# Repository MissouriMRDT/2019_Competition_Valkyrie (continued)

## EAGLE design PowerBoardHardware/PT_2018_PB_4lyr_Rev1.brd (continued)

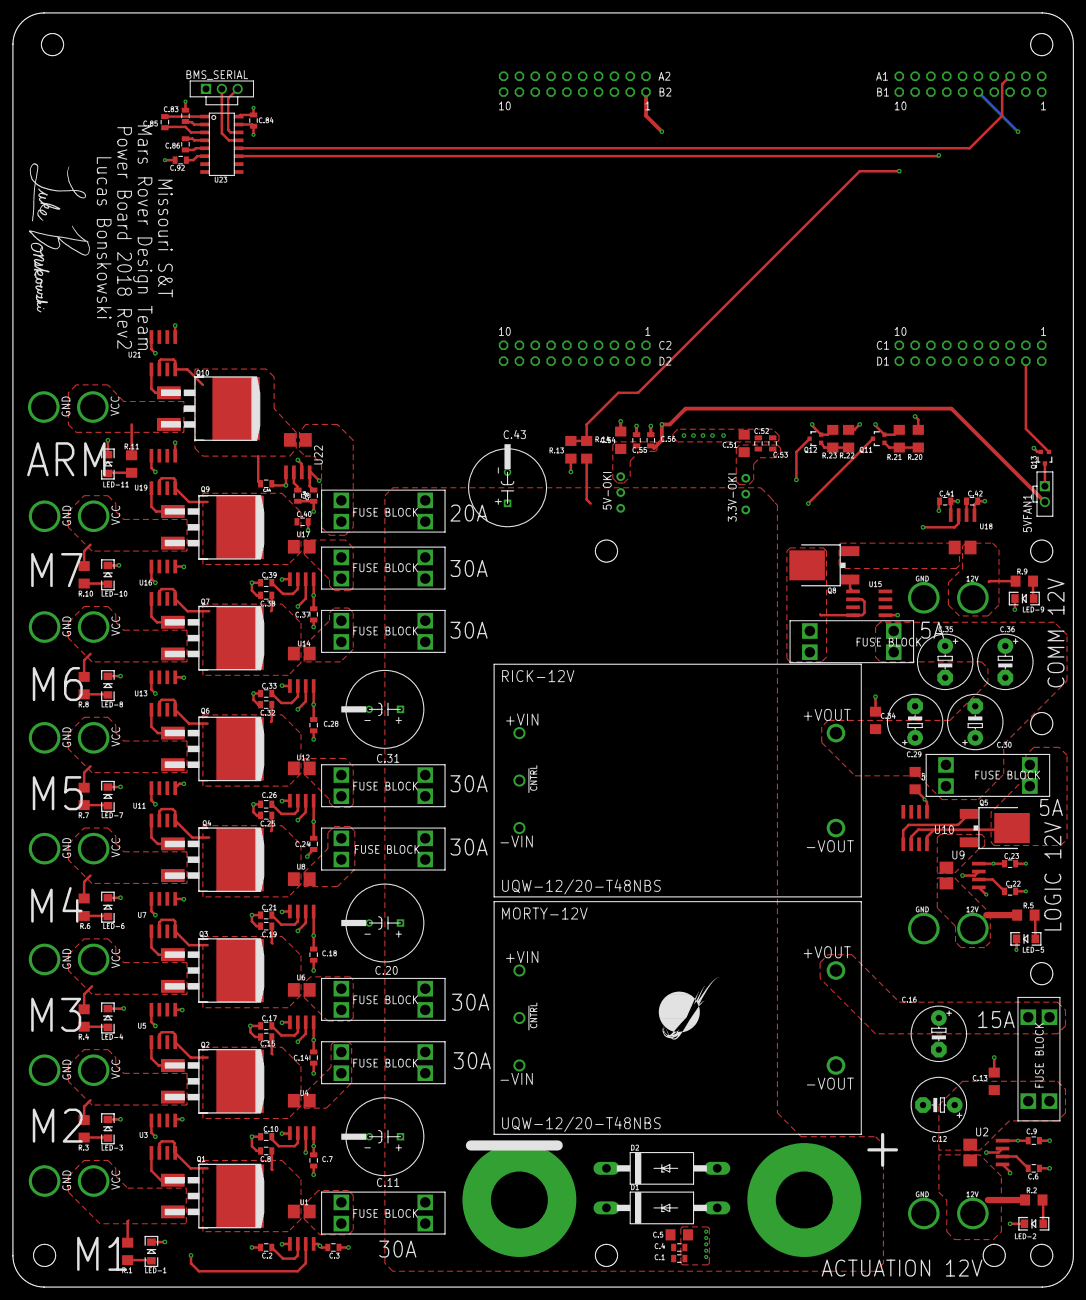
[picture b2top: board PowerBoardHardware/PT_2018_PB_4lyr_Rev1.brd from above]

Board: 4 copper layers, 170.2 x 204.5 mm, 165 parts (0 on the bottom side), 108 nets.

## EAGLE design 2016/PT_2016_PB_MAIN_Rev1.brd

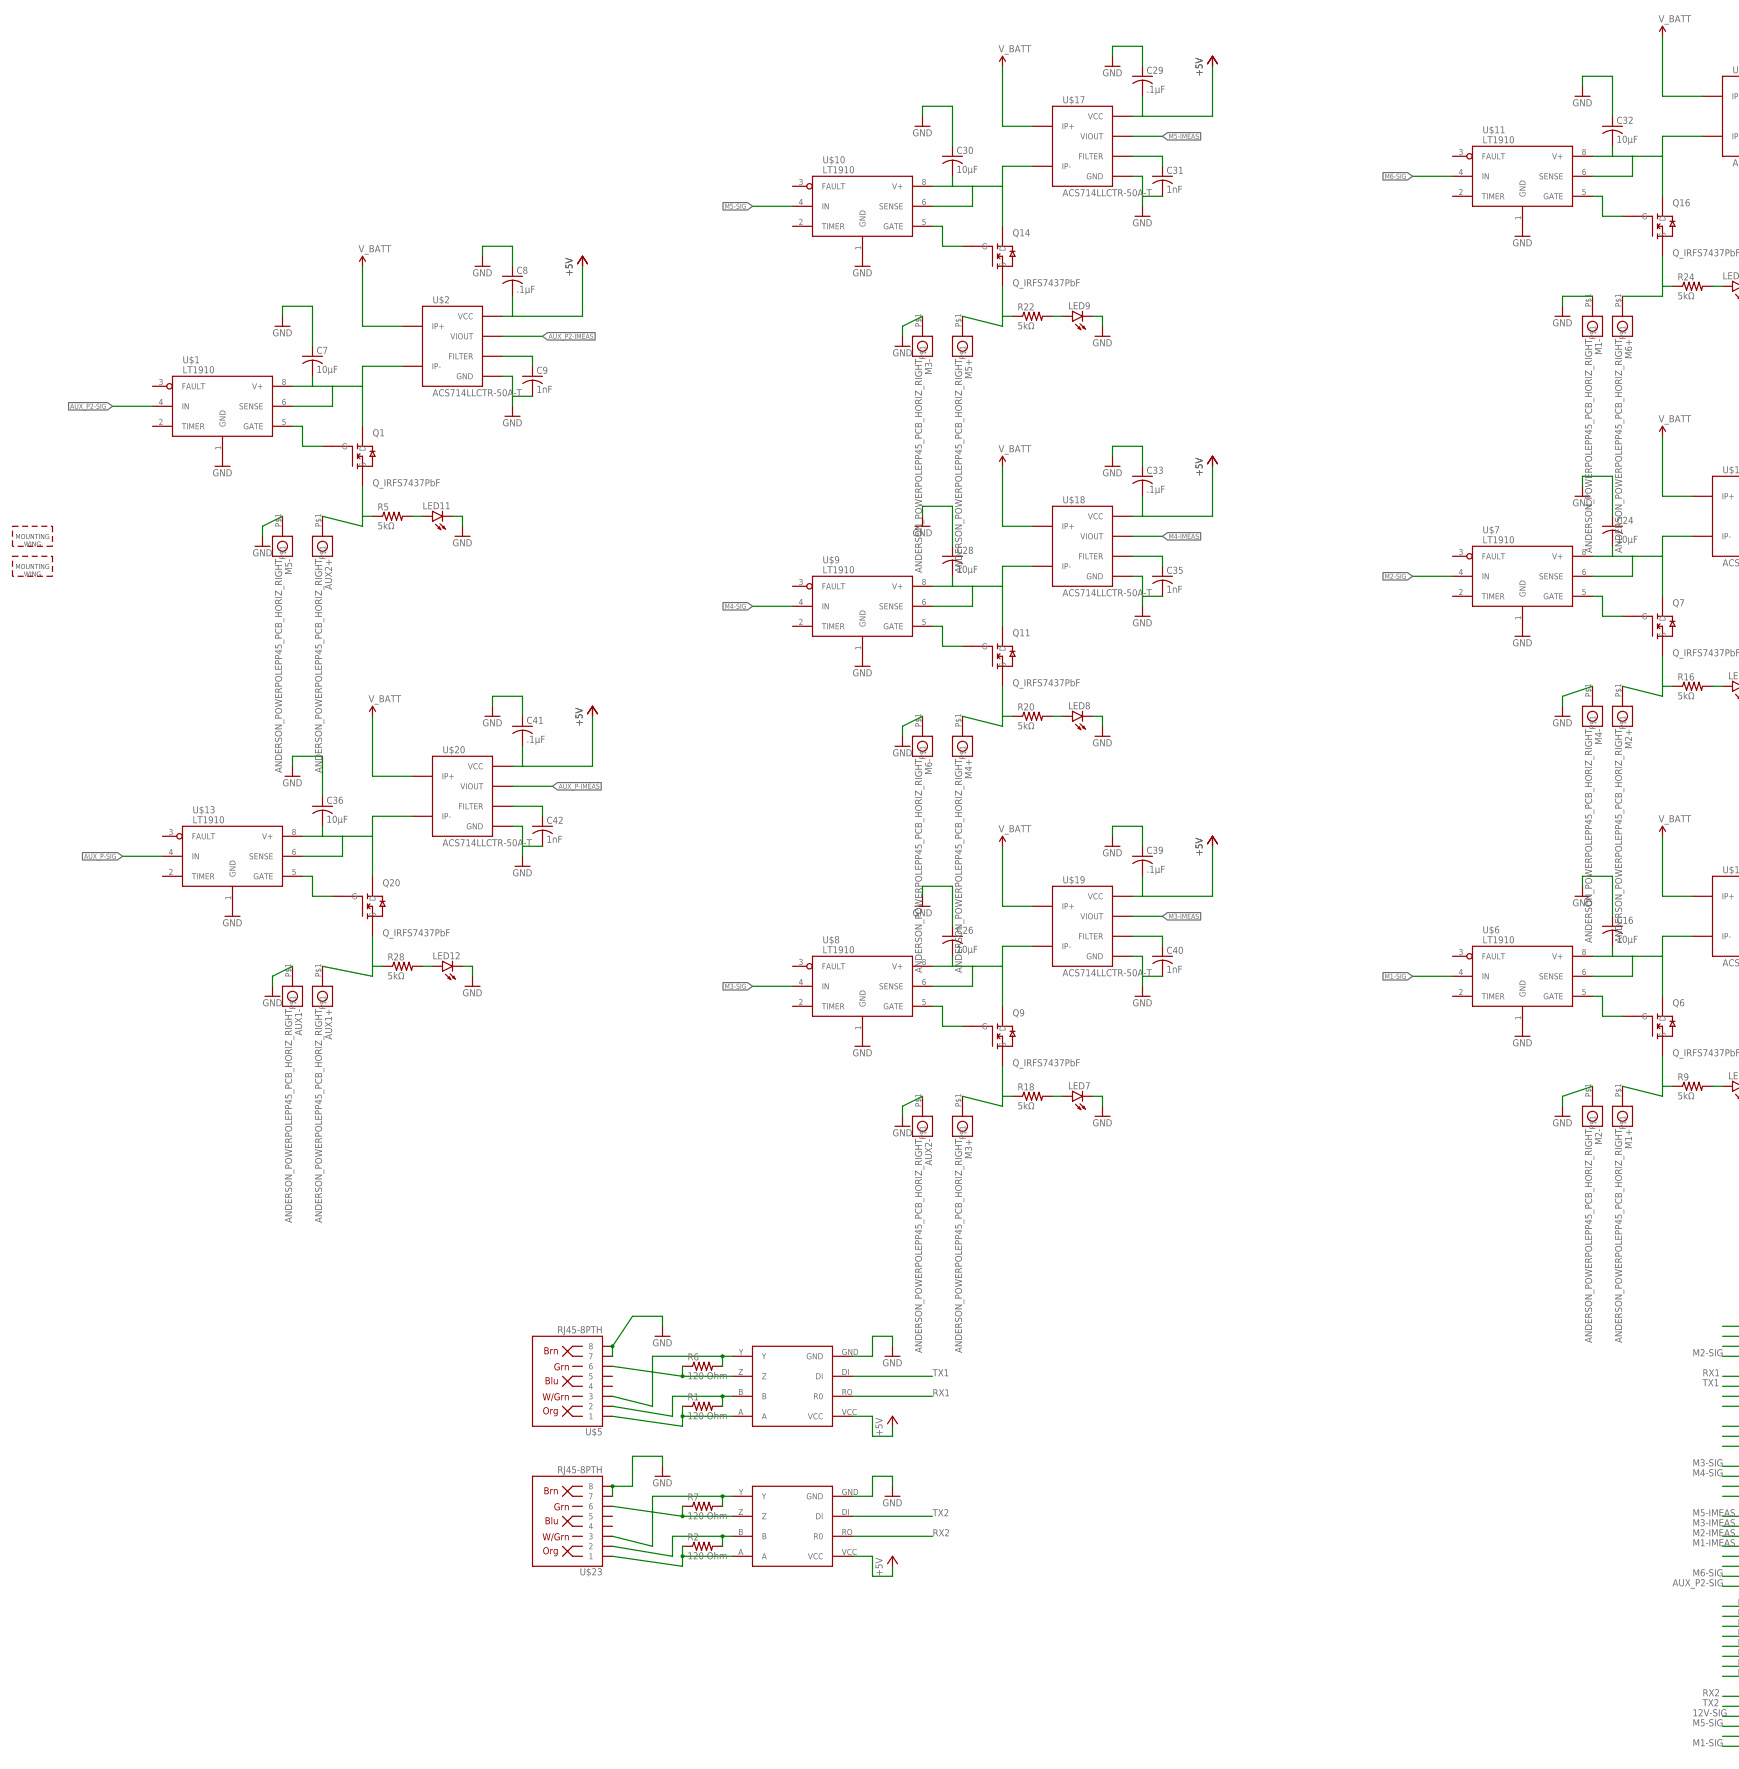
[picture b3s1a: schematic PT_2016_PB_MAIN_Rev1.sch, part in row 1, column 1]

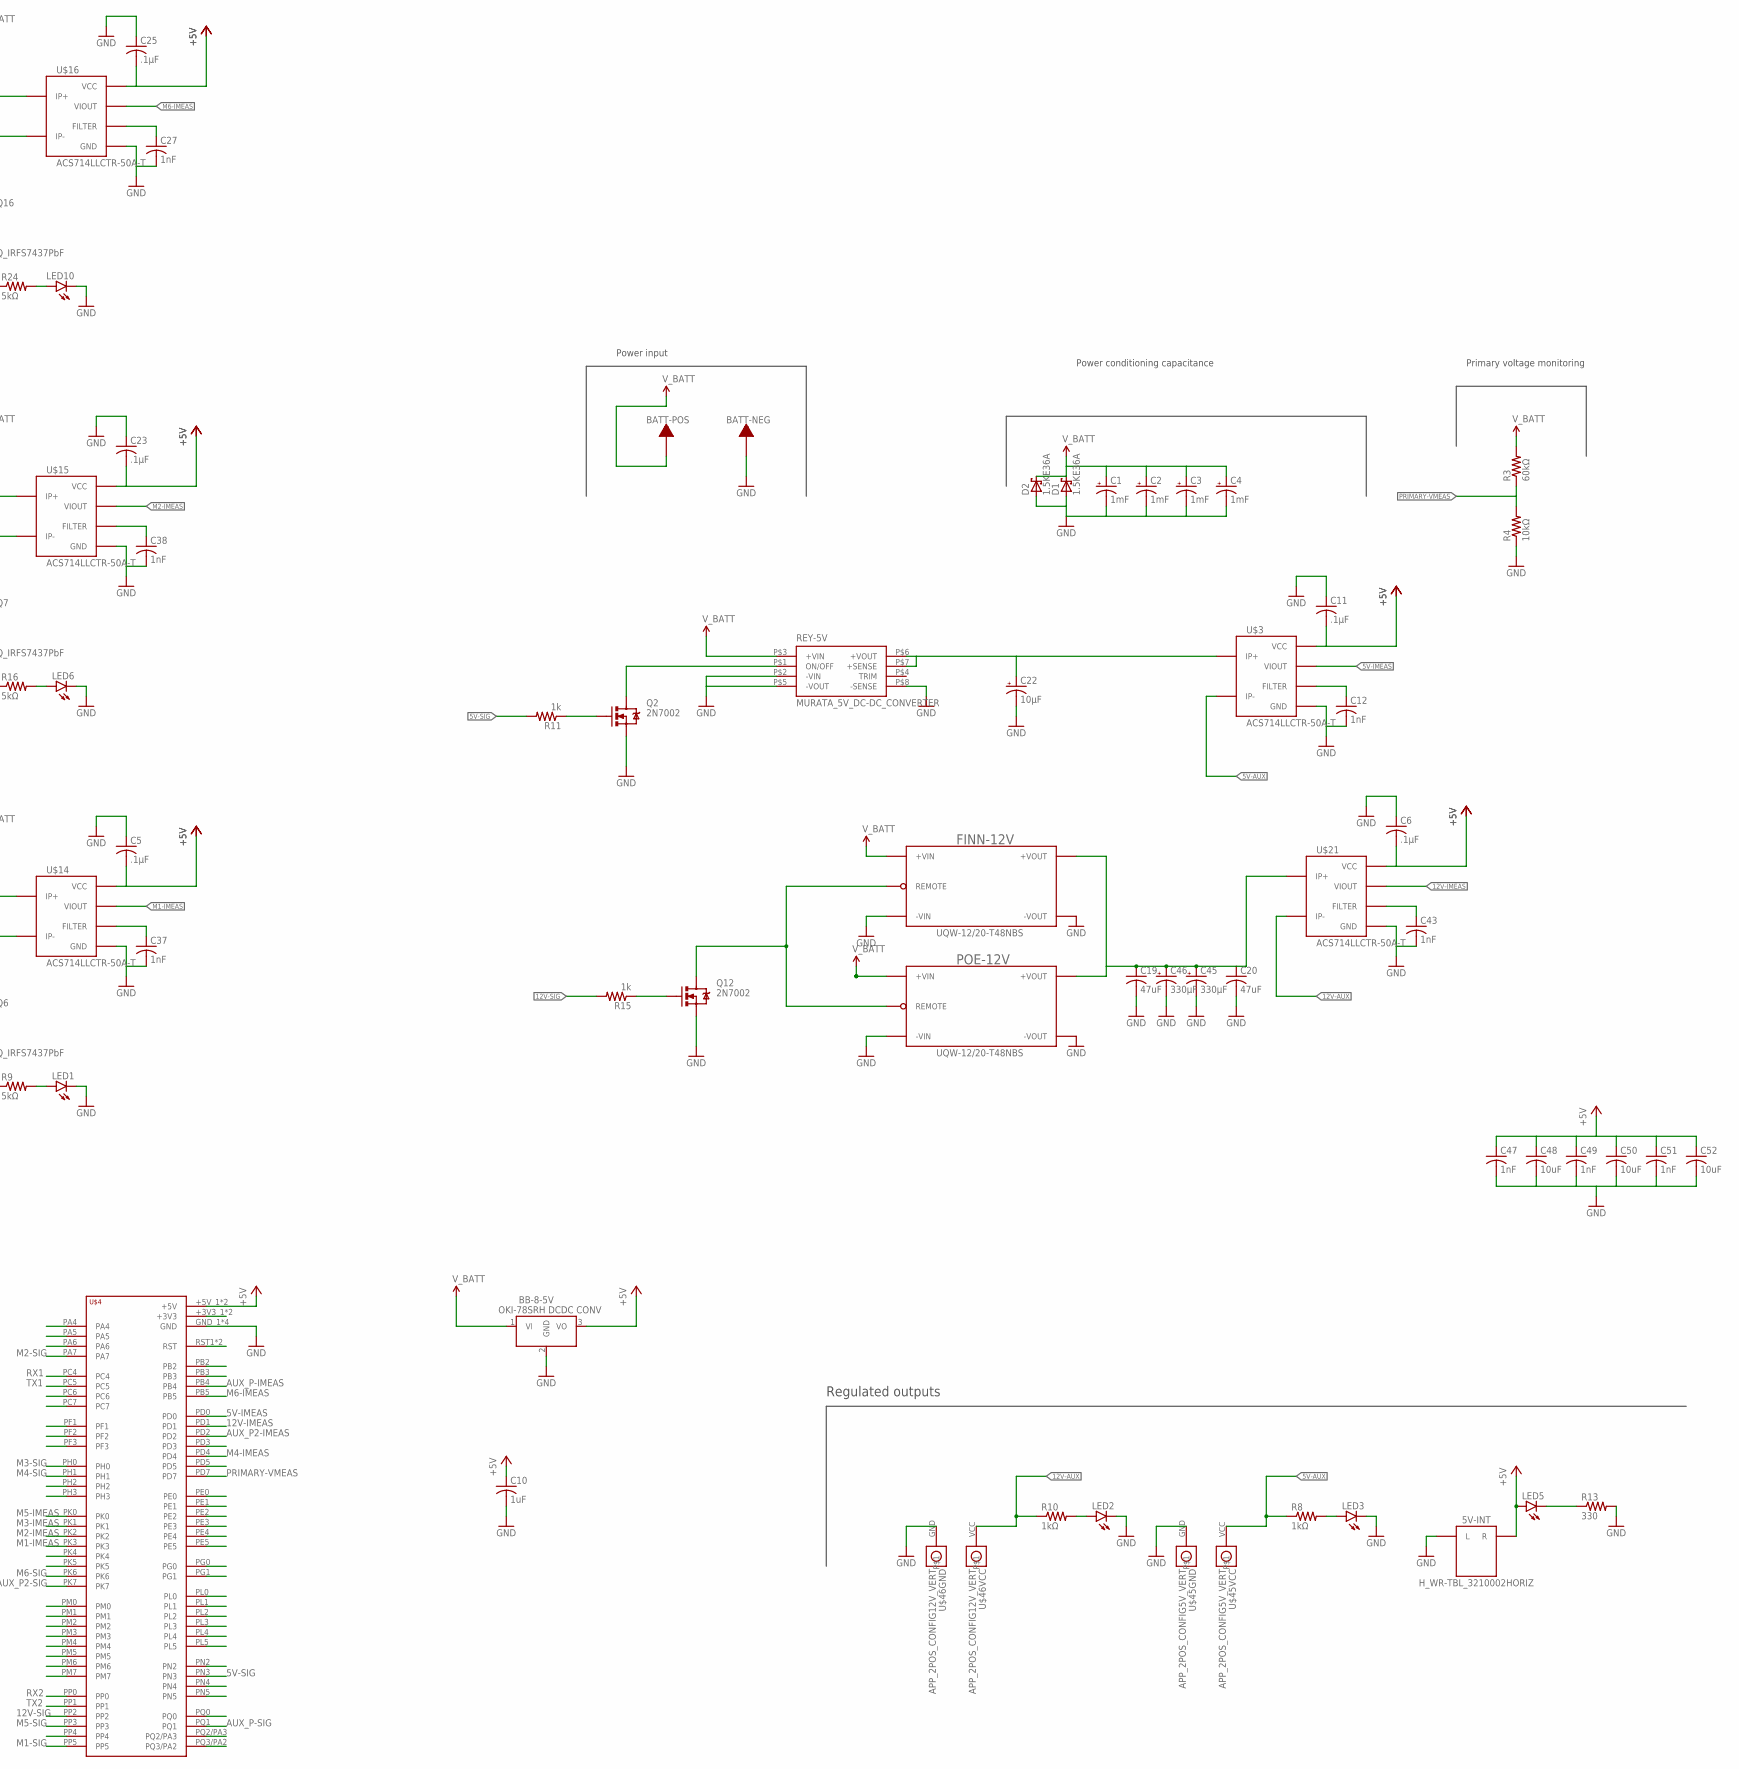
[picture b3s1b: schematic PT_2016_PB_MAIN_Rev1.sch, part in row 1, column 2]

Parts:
5V-INT: H_WR-TBL_3210002HORIZ; 691322110002
AUX1+, AUX1-, AUX2+, AUX2-: ANDERSON_POWERPOLEPP45_PCB_HORIZ_RIGHT; APP45_PCB_HORIZ_RIGHT
BATT-NEG: TERMINAL_HOLE; LARGE_TERMINAL_HOLE
BATT-POS: TERMINAL_HOLE; LARGE_TERMINAL_HOLE
BB-8-5V: Q_OKI-78SR; OKI-78SRH
C1, C2, C3, C4: 1mF; C_12.5MM
C5, C6, C8, C11, C23, C25, C29, C33, C39, C41: .1µF; C1206
C7, C16, C24, C26, C28, C30, C32, C36: 10µF; C1206
C9, C12, C27, C31, C35, C37, C38, C40, C42, C43, C47, C49, C51: 1nF; C1206
C10: 1uF; C1206
C19, C20: 47uF; C1206
C22: 10µF; E5-8,5
C45, C46: 330µF; E5-8,5
C48, C50, C52: 10uF; C1206
D1, D2: 1.5KE36A; CB429-17
FINN-12V: UQW-12/20-T48NBS; U-T48-QB-NO_TRIM
LED1, LED2, LED3, LED5, LED6, LED7, LED8, LED9, LED10, LED11, LED12: LED1206; LED-1206
M1+, M1-, M2+, M2-, M3+, M3-, M4+, M4-, M5+, M5-, M6+, M6-: ANDERSON_POWERPOLEPP45_PCB_HORIZ_RIGHT; APP45_PCB_HORIZ_RIGHT
POE-12V: UQW-12/20-T48NBS; U-T48-QB-NO_TRIM
Q1, Q6, Q7, Q9, Q11, Q14, Q16, Q20: Q_IRFS7437PbF; D2PACK
Q2, Q12: 2N7002; SOT323
R1, R2, R6, R7: 120 Ohm; 1206
R3: 60kΩ; R1206
R4: 10kΩ; R1206
R5, R9, R16, R18, R20, R22, R24, R28: 5kΩ; 1206
R8, R10: 1kΩ; 1206
R11, R15: 1k; R1206
R13: 330; 1206
REY-5V: MURATA_5V_DC-DC_CONVERTER
U$1, U$6, U$7, U$8, U$9, U$10, U$11, U$13: LT1910; SO8
U$2, U$14, U$15, U$16, U$17, U$18, U$19, U$20: ACS714LLCTR-50A-T; SOIC8_ACS711_SKETCH
U$3, U$21: ACS714LLCTR-50A-T; SOIC8_ACS711
U$4: TIVA-C-CONNECTED
U$5, U$23: RJ45-8PTH; RJ45-8
U$12, U$24: MAX3077; MAX3070E
U$41, U$42: APP_MOUTING_WINGHORIZ; APP45_MOUNTING_WING_HORIZ
U$45: APP_2POS_CONFIG5V_VERT; APP45_5V_VERT_CONFIG
U$46: APP_2POS_CONFIG12V_VERT; APP45_12V_VERT_CONFIG

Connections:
5V-AUX: R8.1, U$3.4 (IP-), U$45.VCC
5V-IMEAS: U$3.7 (VIOUT), U$4.PD0
5V-SIG: R11.2, U$4.PN3
12V-AUX: R10.1, U$21.4 (IP-), U$46.VCC
12V-IMEAS: U$4.PD1, U$21.7 (VIOUT)
12V-SIG: R15.2, U$4.PP2
+5V: 5V-INT.R, BB-8-5V.3 (VO), C5.2, C6.2, C8.2, C10.1, C11.2, C23.2, C25.2, C29.2, C33.2, C39.2, C41.2, C47.1, C48.1, C49.1, C50.1, C51.1, C52.1, LED5.A, U$2.8 (VCC), U$3.8 (VCC), U$4.+5V_1 (+5V), U$4.+5V_2 (+5V), U$12.VCC, U$14.8 (VCC), U$15.8 (VCC), U$16.8 (VCC), U$17.8 (VCC), U$18.8 (VCC), U$19.8 (VCC), U$20.8 (VCC), U$21.8 (VCC), U$24.VCC
AUX_P2-IMEAS: U$2.7 (VIOUT), U$4.PD2
AUX_P2-SIG: U$1.4 (IN), U$4.PK7
AUX_P-IMEAS: U$4.PB4, U$20.7 (VIOUT)
AUX_P-SIG: U$4.PQ1, U$13.4 (IN)
GND: 5V-INT.L, AUX1-.P$1, AUX2-.P$1, BATT-NEG.P$1, BB-8-5V.2 (GND), C1.-, C2.-, C3.-, C4.-, C5.1, C6.1, C7.1, C8.1, C9.2, C10.2, C11.1, C12.2, C16.1, C19.2, C20.2, C22.-, C23.1, C24.1, C25.1, C26.1, C27.2, C28.1, C29.1, C30.1, C31.2, C32.1, C33.1, C35.2, C36.1, C37.2, C38.2, C39.1, C40.2, C41.1, C42.2, C43.2, C45.-, C46.-, C47.2, C48.2, C49.2, C50.2, C51.2, C52.2, D1.A, D2.A, FINN-12V.3 (-VIN), FINN-12V.4 (-VOUT), LED1.C, LED2.C, LED3.C, LED6.C, LED7.C, LED8.C, LED9.C, LED10.C, LED11.C, LED12.C, M1-.P$1, M2-.P$1, M3-.P$1, M4-.P$1, M5-.P$1, M6-.P$1, POE-12V.3 (-VIN), POE-12V.4 (-VOUT), Q2.2 (S), Q12.2 (S), R4.1, R13.2, REY-5V.P$2 (-VIN), REY-5V.P$5 (-VOUT), REY-5V.P$8 (-SENSE), U$1.1 (GND), U$2.5 (GND), U$3.5 (GND), U$4.GND_1 (GND), U$4.GND_2 (GND), U$4.GND_3 (GND), U$4.GND_4 (GND), U$5.7, U$5.8, U$6.1 (GND), U$7.1 (GND), U$8.1 (GND), U$9.1 (GND), U$10.1 (GND), U$11.1 (GND), U$12.GND, U$13.1 (GND), U$14.5 (GND), U$15.5 (GND), U$16.5 (GND), U$17.5 (GND), U$18.5 (GND), U$19.5 (GND), U$20.5 (GND), U$21.5 (GND), U$23.7, U$23.8, U$24.GND, U$45.GND, U$46.GND
M1-IMEAS: U$4.PK3, U$14.7 (VIOUT)
M1-SIG: U$4.PP5, U$6.4 (IN)
M2-IMEAS: U$4.PK2, U$15.7 (VIOUT)
M2-SIG: U$4.PA7, U$7.4 (IN)
M3-IMEAS: U$4.PK1, U$19.7 (VIOUT)
M3-SIG: U$4.PH0, U$8.4 (IN)
M4-IMEAS: U$4.PD4, U$18.7 (VIOUT)
M4-SIG: U$4.PH1, U$9.4 (IN)
M5-IMEAS: U$4.PK0, U$17.7 (VIOUT)
M5-SIG: U$4.PP3, U$10.4 (IN)
M6-IMEAS: U$4.PB5, U$16.7 (VIOUT)
M6-SIG: U$4.PK6, U$11.4 (IN)
unnamed: C37.1, U$14.6 (FILTER)
unnamed: C38.1, U$15.6 (FILTER)
unnamed: FINN-12V.2 (REMOTE), POE-12V.2 (REMOTE), Q12.3 (D)
unnamed: LED5.C, R13.1
unnamed: C22.+, REY-5V.P$6 (+VOUT), REY-5V.P$7 (+SENSE), U$3.1 (IP+)
unnamed: C7.2, Q1.TAB (D), U$1.6 (SENSE), U$1.8 (V+), U$2.4 (IP-)
unnamed: AUX2+.P$1, Q1.2 (S), R5.1
unnamed: C43.1, U$21.6 (FILTER)
unnamed: Q1.1 (G), U$1.5 (GATE)
unnamed: LED11.A, R5.2
unnamed: C9.1, U$2.6 (FILTER)
unnamed: C27.1, U$16.6 (FILTER)
unnamed: C31.1, U$17.6 (FILTER)
unnamed: C35.1, U$18.6 (FILTER)
unnamed: C40.1, U$19.6 (FILTER)
unnamed: C42.1, U$20.6 (FILTER)
unnamed: C24.2, Q7.TAB (D), U$7.6 (SENSE), U$7.8 (V+), U$15.4 (IP-)
unnamed: M2+.P$1, Q7.2 (S), R16.1
unnamed: Q7.1 (G), U$7.5 (GATE)
unnamed: LED6.A, R16.2
unnamed: C19.1, C20.1, C45.+, C46.+, FINN-12V.8 (+VOUT), POE-12V.8 (+VOUT), U$21.1 (IP+)
unnamed: LED3.A, R8.2
unnamed: C12.1, U$3.6 (FILTER)
unnamed: LED1.A, R9.2
unnamed: C16.2, Q6.TAB (D), U$6.6 (SENSE), U$6.8 (V+), U$14.4 (IP-)
unnamed: M1+.P$1, Q6.2 (S), R9.1
unnamed: Q6.1 (G), U$6.5 (GATE)
unnamed: Q2.3 (D), REY-5V.P$1 (ON/OFF)
unnamed: C26.2, Q9.TAB (D), U$8.6 (SENSE), U$8.8 (V+), U$19.4 (IP-)
unnamed: M3+.P$1, Q9.2 (S), R18.1
unnamed: LED2.A, R10.2
unnamed: Q9.1 (G), U$8.5 (GATE)
unnamed: Q2.1 (G), R11.1
unnamed: LED7.A, R18.2
unnamed: C28.2, Q11.TAB (D), U$9.6 (SENSE), U$9.8 (V+), U$18.4 (IP-)
unnamed: M4+.P$1, Q11.2 (S), R20.1
unnamed: Q11.1 (G), U$9.5 (GATE)
unnamed: LED8.A, R20.2
unnamed: C30.2, Q14.TAB (D), U$10.6 (SENSE), U$10.8 (V+), U$17.4 (IP-)
unnamed: M5+.P$1, Q14.2 (S), R22.1
unnamed: Q14.1 (G), U$10.5 (GATE)
unnamed: LED9.A, R22.2
unnamed: C32.2, Q16.TAB (D), U$11.6 (SENSE), U$11.8 (V+), U$16.4 (IP-)
unnamed: M6+.P$1, Q16.2 (S), R24.1
unnamed: Q16.1 (G), U$11.5 (GATE)
unnamed: LED10.A, R24.2
unnamed: C36.2, Q20.TAB (D), U$13.6 (SENSE), U$13.8 (V+), U$20.4 (IP-)
unnamed: AUX1+.P$1, Q20.2 (S), R28.1
unnamed: Q20.1 (G), U$13.5 (GATE)
unnamed: LED12.A, R28.2
unnamed: U$4.+3V3_1 (+3V3), U$4.+3V3_2 (+3V3)
unnamed: U$4.RST1 (RST), U$4.RST_2 (RST)
unnamed: Q12.1 (G), R15.1
PRIMARY-VMEAS: R3.1, R4.2, U$4.PD7
REC+: R1.1, U$5.1, U$12.A
REC+1: R2.1, U$23.1, U$24.A
REC-: R1.2, U$5.2, U$12.B
REC-1: R2.2, U$23.2, U$24.B
RX1: U$4.PC4, U$12.RO (R0)
RX2: U$4.PP0, U$24.RO (R0)
TRANS+: R6.2, U$5.3, U$12.Y
TRANS+1: R7.2, U$23.3, U$24.Y
TRANS-: R6.1, U$5.6, U$12.Z
TRANS-1: R7.1, U$23.6, U$24.Z
TX1: U$4.PC5, U$12.DI
TX2: U$4.PP1, U$24.DI
V_BATT: BATT-POS.P$1, BB-8-5V.1 (VI), C1.+, C2.+, C3.+, C4.+, D1.C, D2.C, FINN-12V.1 (+VIN), POE-12V.1 (+VIN), R3.2, REY-5V.P$3 (+VIN), U$2.1 (IP+), U$14.1 (IP+), U$15.1 (IP+), U$16.1 (IP+), U$17.1 (IP+), U$18.1 (IP+), U$19.1 (IP+), U$20.1 (IP+)

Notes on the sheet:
Primary voltage monitoring
Power conditioning capacitance
Power input
Regulated outputs

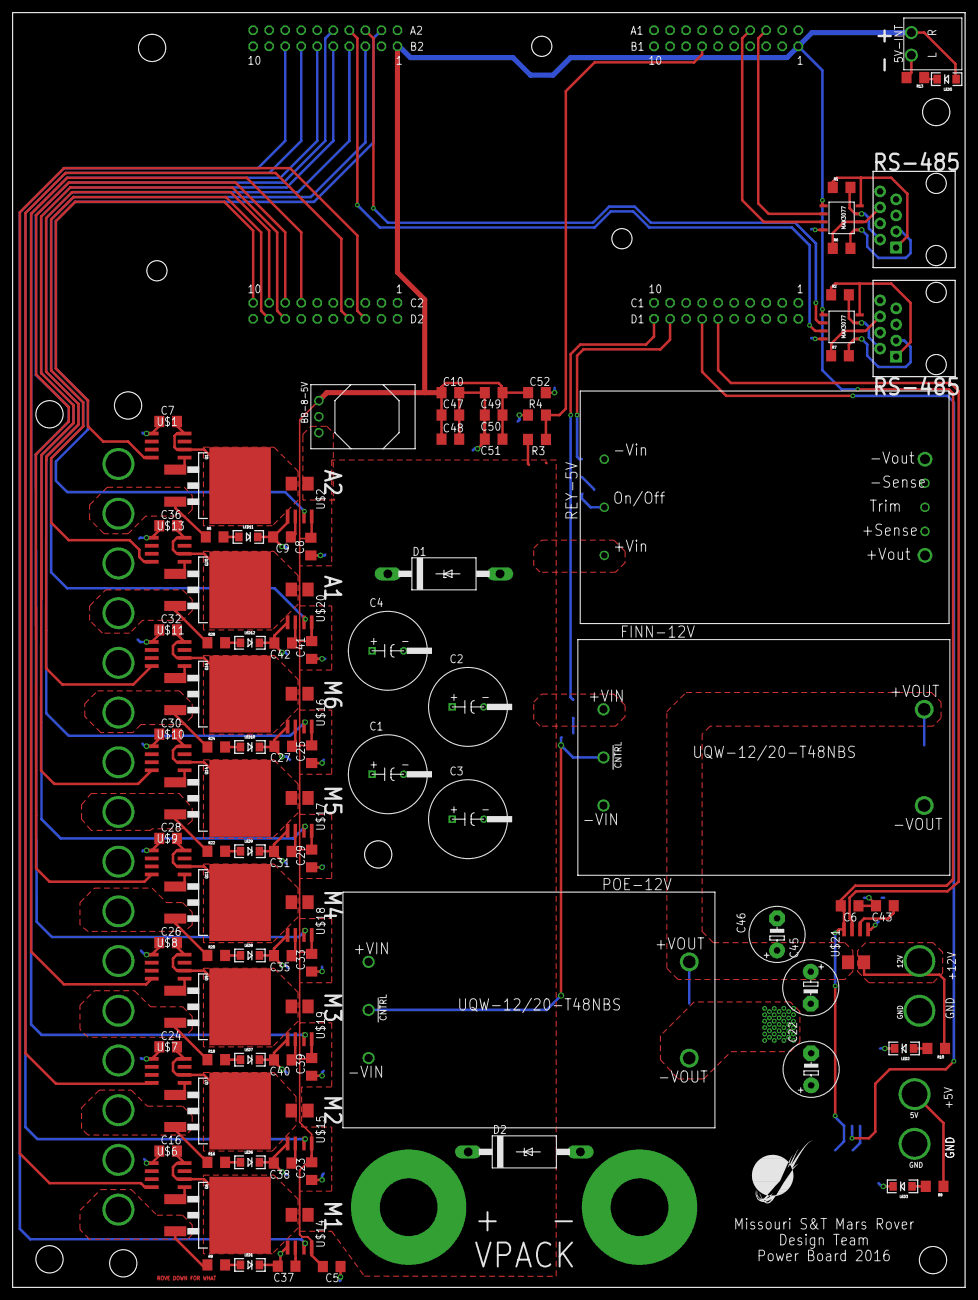
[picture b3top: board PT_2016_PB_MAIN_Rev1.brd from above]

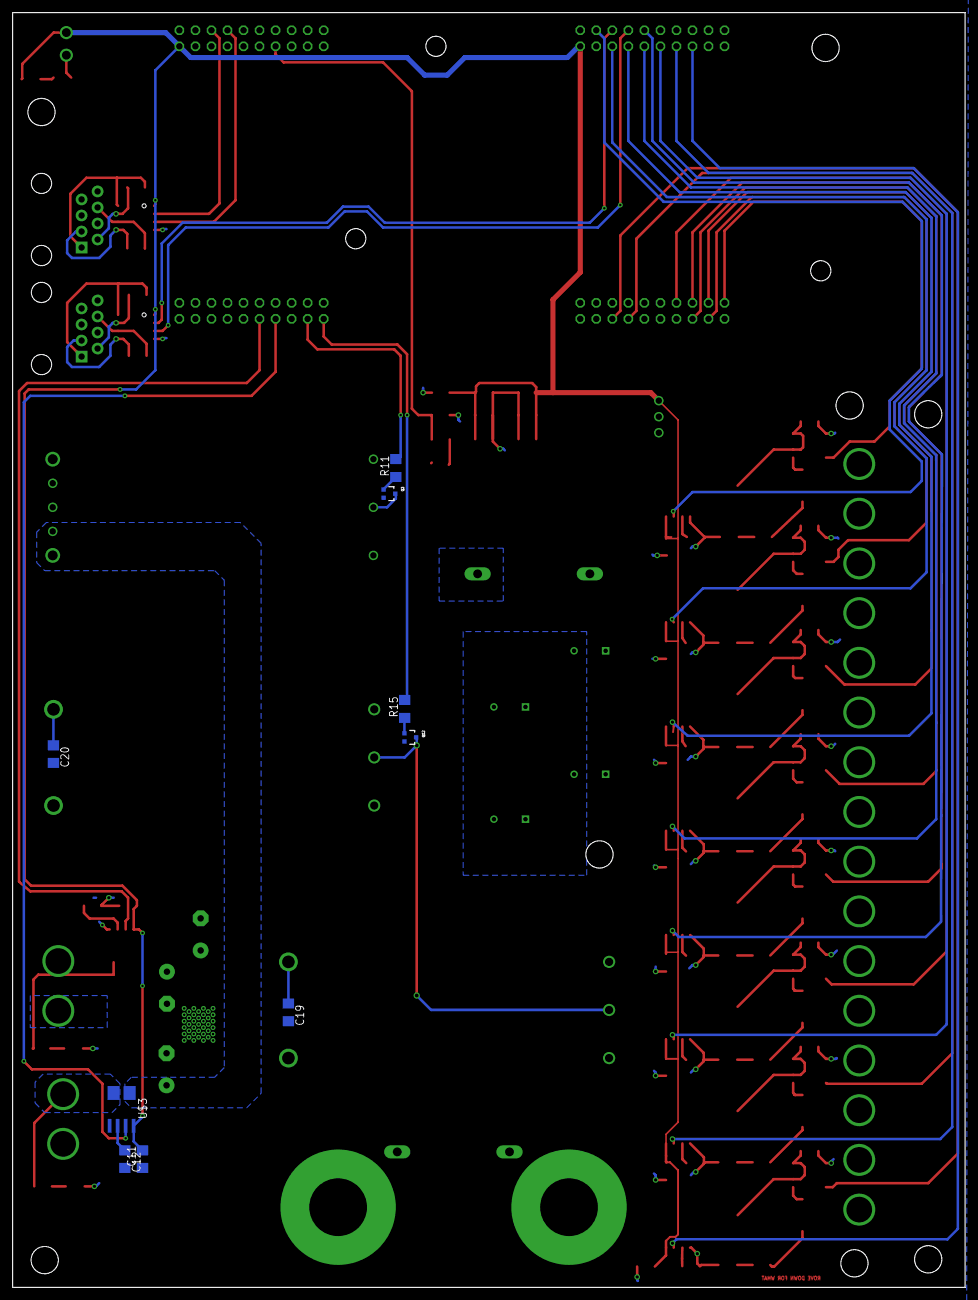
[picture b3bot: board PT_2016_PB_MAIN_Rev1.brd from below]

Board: 2 copper layers, 150.9 x 201.9 mm, 137 parts (11 on the bottom side), 91 nets.

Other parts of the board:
U$22: MRDT_LOGO

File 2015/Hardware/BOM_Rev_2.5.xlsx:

Qty | Value | Device | Package | Parts | Description | DIGIKEY_PN | PROD_ID | VALUE
1 | We have these | Ferrite Bead | L8530M | L3 | INDUCTOR, American symbol | We already have them
13 | LED | LED | LED-1206 | LED1, LED2, LED3, LED4, LED5, LED6, LED7, LED8, LED9, LED10, LED11, LED12, LED13 | LEDs | 754-1171-1-ND
9 | .1µF | Capacitor | C1206 | C5, C6, C23, C25, C29, C33, C39, C41, C44 | CAPACITOR, American symbol | 399-1249-1-ND
2 | 1.5KE36A | TVS Diode | CB429-17 | D1, D2 | DIODE | 1.5KE36A-TPMSCT-ND | Should have plenty
1 | 10k Ohm | Resistor | R1206 | R2, R4 | RESISTOR, American symbol | P10.0KFCT-ND
16 | 10 µF | Capacitor | C1206 | C10, C15, C16, C24, C26, C28, C30, C32, C34, C36, C8, C9, C11, C48, C50, C52 | CAPACITOR, American symbol | 587-3248-1-ND
2 | 120 Ohm | Resistor | 1206 | R5, R6 | Resistor | P120FCT-ND | Should have plenty
4 | 1k Ohm | Resistor | 1206 | R10, R11, R1, R15 | Resistor | P1.00KFCT-ND | Should have plenty
4 | 1mF | Capacitor | C_12.5MM | C1, C2, C3, C4 | Alum Elect. Cap with 10mm diameter, 5mm lead spacing and 0.7mm lead diameter | UVY1H102MHD-ND | Should have plenty
11 | 1nF | Capacitor | C1206 | C27, C31, C35, C37, C38, C40, C42, C43, C47, C49, C51 | CAPACITOR, American symbol | 399-1147-1-ND
2 | 1 µF | Capacitor | C1206 | C7, C13, C14 | CAPACITOR, American symbol | 445-1423-1-ND
1 | 200mA/50V | Small MOSFET | SOT23-3 | Q2 | Common NMOSFET Parts | BSS138CT-ND | TRANS-00830 | 200mA/50V
1 | 21k Ohm | Resistor | R1206 | R8 | RESISTOR, American symbol | P21.0KFCT-ND
1 | 2N7002 | Small MOSFET | SOT323 | Q12 | Common NMOSFET Parts | 2N7002WT1GOSCT-ND | TRANS-11151
1 | 32U4_BREAKOUT | 32U4_BREAKOUT | 32U4_MCU_DIP | U$1
2 | 330 Ohm | Resistor | 1206 | R12, R13 | Resistor | RHM330CJCT-ND
4 | 330µF | Capacitor | E5-8,5 | C21, C22, C45, C46 | POLARIZED CAPACITOR, American symbol | 493-1042-ND
5 | 47uF | Capacitor | C1206 | C19, C20, C17, C18, C12 | CAPACITOR, American symbol | 490-9967-1-ND
1 | 590 Ohm | Resistor | R1206 | R7 | RESISTOR, American symbol | P590FCT-ND
8 | 5k ohm | Resistor | 1206 | R9, R16, R18, R20, R22, R24, R26, R28 | Resistor | 541-5.1KECT-ND
1 | 60k ohm | Resistor | R1206 | R3 | RESISTOR, American symbol | P60.4KFCT-ND
8 | ACS714LLCTR-50A-T | Current Sensor | SOIC8_ACS711 | U$21, U$14, U$15, U$16, U$17, U$18, U$19, U$20 | Sketch variant has increased clearance for traces. | 620-1683-1-ND
1 | BUZZERSMD2 | Buzzer | BUZZER-CCV | SG1 | Buzzer 12mm
1 | D_SD12T1G | 5V TVS Zener Diode | SOD-323 | U$2 | 5V Zener | SD05T1GOSCT-ND
1 | D_SD12T1G | 12V TVS Zener Diode | SOD-323 | U$5 | 12V Zener | SD12T1GOSCT-ND
8 | H_20020618-M02HORIZ | 30A Terminal | 20020618-M02 | 12V-AUX, AUX_P, MOTOR_1, MOTOR_2, MOTOR_3, MOTOR_4, MOTOR_5, MOTOR_6 | High amp pluggable screw terminal from FCI. Rated up to 32A | 609-3951-ND | Should have plenty
4 | H_WR-TBL_321*0002HORIZ | 10A Terminal | 691322110002 | 5V-EXT, 5V-INT, 12V-CRIT, ARM_P | Wurth Electronic's 2-pin 10A pluggable screw terminal headers. Vertical and Hor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 | 732-2769-ND
8 | LT1910 | MOSFET Driver | SO8 | U$6, U$7, U$8, U$9, U$10, U$11, U$12, U$13 |  | LT1910IS8#PBF-ND | Buy extra
1 | MAX3077 | RS-485 Transeiver | MAX3070E | U$3
3 | Q_ACS711LC | Current Sensor | SOIC8_ACS711 | Q1, Q4, Q5 | Â±12.5A or Â±25A Hall-effect current transducer. SOIC-8 Package with fused pads. | 620-1372-1-ND
1 | Q_FDT86102LZ | MOSFET | SOT-223 | Q18 |  | FDT86102LZFSCT-ND
7 | Q_IRFS7437PbF | MOSFET | D2PACK | Q6, Q7, Q9, Q11, Q14, Q16, Q20 | 40V 195A N-CH MOSFET switch with heatsink | IRFS7437PBF-ND | Buy extra
1 | Q_OKI-78SR | Board-Mount Power Electronic Converter | OKI-78SRH | OKI-78SR-5/1.5-W36H | 4.95W DC/DC Converter | 811-2692-ND
2 | Q_PTN78020WAH | Board-Mount Power Electronic Converter | R_PDSS-T7 | DOOKU-12V-CRIT, VADER-5V-EXT | TI DC/DC converter 36Vin - Adjustable output | 296-20515-ND
1 | RJ45-8PTH | RJ45 Jack | RJ45-8 | U$4 | RJ45 Jack |  | should have plenty
2 | UQW-12/20-T48NBS | Board-Mount Power Electronic Converter | U-T48-QB-NO_TRIM | PALPATINE-12V, SIDEOUS-12V | Murata 12V DC/DC Converter- 20 Amp | 811-2966-ND

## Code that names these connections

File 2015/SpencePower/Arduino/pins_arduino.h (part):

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
// ATMEL ATMEGA32U4 / ARDUINO LEONARDO
//
// D0				PD2					RXD1/INT2
// D1				PD3					TXD1/INT3
// D2				PD1		SDA			SDA/INT1
// D3#				PD0		PWM8/SCL	OC0B/SCL/INT0
// D4		A6		PD4					ADC8
// D5#				PC6		???			OC3A/#OC4A
// D6#		A7		PD7		FastPWM		#OC4D/ADC10
// D7				PE6					INT6/AIN0
//
// D8		A8		PB4					ADC11/PCINT4
// D9#		A9		PB5		PWM16		OC1A/#OC4B/ADC12/PCINT5
// D10#		A10		PB6		PWM16		OC1B/0c4B/ADC13/PCINT6
// D11#				PB7		PWM8/16		0C0A/OC1C/#RTS/PCINT7
// D12		A11		PD6					T1/#OC4D/ADC9
// D13#				PC7		PWM10		CLK0/OC4A
//
// A0		D18		PF7					ADC7
// A1		D19		PF6					ADC6
// A2		D20 	PF5					ADC5
// A3		D21 	PF4					ADC4
// A4		D22		PF1					ADC1
// A5		D23 	PF0					ADC0
//
// New pins D14..D17 to map SPI port to digital pins
//
// MISO		D14		PB3					MISO,PCINT3
// SCK		D15		PB1					SCK,PCINT1
// MOSI		D16		PB2					MOSI,PCINT2
// SS		D17		PB0					RXLED,SS/PCINT0
//
// TXLED			PD5
// RXLED		    PB0
// HWB				PE2					HWB

// these arrays map port names (e.g. port B) to the
// appropriate addresses for various functions (e.g. reading
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};

const uint8_t PROGMEM digital_pin_to_port_PGM[] = {
	PD, // D0 - PD2
	PD,	// D1 - PD3
	PD, // D2 - PD1
	PD,	// D3 - PD0
	PD,	// D4 - PD4
	PC, // D5 - PC6
	PD, // D6 - PD7
	PE, // D7 - PE6
	
	PB, // D8 - PB4
	PB,	// D9 - PB5
	PB, // D10 - PB6
	PB,	// D11 - PB7
	PD, // D12 - PD6
	PC, // D13 - PC7
	
	PB,	// D14 - MISO - PB3
	PB,	// D15 - SCK - PB1
	PB,	// D16 - MOSI - PB2
	PB,	// D17 - SS - PB0
	
	PF,	// D18 - A0 - PF7
	PF, // D19 - A1 - PF6
	PF, // D20 - A2 - PF5
	PF, // D21 - A3 - PF4
	PF, // D22 - A4 - PF1
	PF, // D23 - A5 - PF0
	
	PD, // D24 / D4 - A6 - PD4
	PD, // D25 / D6 - A7 - PD7
	PB, // D26 / D8 - A8 - PB4
	PB, // D27 / D9 - A9 - PB5
	PB, // D28 / D10 - A10 - PB6
	PD, // D29 / D12 - A11 - PD6
};

const uint8_t PROGMEM digital_pin_to_bit_mask_PGM[] = {
	_BV(2), // D0 - PD2
	_BV(3),	// D1 - PD3
	_BV(1), // D2 - PD1
	_BV(0),	// D3 - PD0
	_BV(4),	// D4 - PD4
	_BV(6), // D5 - PC6
	_BV(7), // D6 - PD7
	_BV(6), // D7 - PE6
	
	_BV(4), // D8 - PB4
	_BV(5),	// D9 - PB5
	_BV(6), // D10 - PB6
	_BV(7),	// D11 - PB7
	_BV(6), // D12 - PD6
	_BV(7), // D13 - PC7
	
	_BV(3),	// D14 - MISO - PB3
	_BV(1),	// D15 - SCK - PB1
	_BV(2),	// D16 - MOSI - PB2
	_BV(0),	// D17 - SS - PB0
	
	_BV(7),	// D18 - A0 - PF7
	_BV(6), // D19 - A1 - PF6
	_BV(5), // D20 - A2 - PF5
	_BV(4), // D21 - A3 - PF4
	_BV(1), // D22 - A4 - PF1
	_BV(0), // D23 - A5 - PF0
	
	_BV(4), // D24 / D4 - A6 - PD4
	_BV(7), // D25 / D6 - A7 - PD7
	_BV(4), // D26 / D8 - A8 - PB4
	_BV(5), // D27 / D9 - A9 - PB5
	_BV(6), // D28 / D10 - A10 - PB6
	_BV(6), // D29 / D12 - A11 - PD6
};

const uint8_t PROGMEM digital_pin_to_timer_PGM[] = {
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};

const uint8_t PROGMEM analog_pin_to_channel_PGM[] = {
	7,	// A0				PF7					ADC7
	6,	// A1				PF6					ADC6	
	5,	// A2				PF5					ADC5	
	4,	// A3				PF4					ADC4
	1,	// A4				PF1					ADC1	
	0,	// A5				PF0					ADC0	
	8,	// A6		D4		PD4					ADC8
	10,	// A7		D6		PD7					ADC10
	11,	// A8		D8		PB4					ADC11
	12,	// A9		D9		PB5					ADC12
	13,	// A10		D10		PB6					ADC13
	9	// A11		D12		PD6					ADC9
};

#endif /* ARDUINO_MAIN */
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
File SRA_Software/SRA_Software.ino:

//Code: Austin Christman
//SRA Software
#include "Adafruit_Sensor.h"
#include "src/DHT/DHT_U.h" //AM2302 Sensor .h files
#include "src/DHT/DHT.h"
#include "src/SHT-XX/SHT1x.h"// SHT-10 Sensor .h files
#include <math.h>


//Rover .h Files
#include "RoveComm.h"
#include "src/Spectrometer/Spectrometer.h"


//pin layout for Tiva C w/ tm4c129
#define SOIL_DATA_PIN          PE_5// Pin located in section X_9:A1, pin PE5
#define CCD_INT_PIN            PE_0// Pin located in section X_9:B1, pin PE0
#define METHANE_VOUT_PIN       PE_2// Pin located in section X_9:B1, pin PE2
#define ATM_DOUT_PIN           PN_2// Pin located in section X_9:D1, pin PN2
#define SW_FLAG1_PIN           PP_4// Pin located in section X_7:A2, pin PP4
#define SW_FLAG2_PIN           PN_5// Pin located in section X_7:A2, pin PN5
#define SW_ERROR_PIN           PN_4// Pin located in section X_7:A2, pin PN4
#define SOIL_SCK_PIN           PB_5// Pin located in seciotn X_7:B2, pin PB5
#define CCD_OS_PIN             A19 // Pin located in section X_7:B2, pin PK3
#define UV_TOGGLE_PIN          PP_5// Pin located in section X_7:D2, pin PP5
#define DHTTYPE                DHT22 // DHT 22 sensor/AM2302 sensor

#define METHANE_ADC_LOW        950 //Value at NewMexico
#define METHANE_ADC_HIGH       1000 
#define METHANE_ACTUAL_LOW     1700 //Average ppb
#define METHANE_ACTUAL_HIGH    1900 //ppb
//#define METHANE_ACTUAL_LOW     1866 //Average ppb
//#define METHANE_ACTUAL_HIGH    970000000 //ppb

int   sensorValue = 0;
uint32_t   methanePpm = 0;
float humidity_atm = 0;
float temperature_atm = 0;
float temperature_soil = 0;
float moisture = 0;


//Rovecomm
RoveCommEthernetUdp Rovecomm;
rovecomm_packet packet;


//delay of 5ms
#define ROVECOMM_DELAY    5

SHT1x th_sensor(SOIL_DATA_PIN, SOIL_SCK_PIN);
DHT dht(ATM_DOUT_PIN, DHTTYPE);

void setup() 
{
  Serial.begin(115200);
  delay(100);
  //Serial.println("Serial Begun");
  Rovecomm.begin(RC_SRASENSORSBOARD_FOURTHOCTET);  // SRA board IP: 138
  delay(ROVECOMM_DELAY);
  //Serial.println("Sensors Begin");
  pinMode(UV_TOGGLE_PIN, OUTPUT);
  pinMode(SW_ERROR_PIN, OUTPUT);
  pinMode(SW_FLAG1_PIN, OUTPUT);
  pinMode(SW_FLAG2_PIN, OUTPUT);

  pinMode(METHANE_VOUT_PIN, INPUT);
  
  //inizalise all output pins outputs and input.
  spectrometerSetup(A19);
  dht.begin();
}

void loop() 
{ 
    
  readAM2302();
  mthnSensorMQ4();
  //  readSHT10();  
  indicateSensorErrorAM2302(humidity_atm, temperature_atm);
  
  uint16_t SRADATA[RC_SRASENSORSBOARD_SENSORDATA_DATACOUNT];
  SRADATA[RC_SRASENSORSBOARD_SENSORDATA_AIRTENTRY]=100*temperature_atm;
  SRADATA[RC_SRASENSORSBOARD_SENSORDATA_AIRMENTRY]=100*humidity_atm;
  SRADATA[RC_SRASENSORSBOARD_SENSORDATA_SOILTENTRY]=1;//100*moisture;
  SRADATA[RC_SRASENSORSBOARD_SENSORDATA_SOILMENTRY]=1;//100*temperature_soil;
  SRADATA[RC_SRASENSORSBOARD_SENSORDATA_METHANEENTRY]= (uint16_t)methanePpm;
  packet = Rovecomm.read();
  Serial.println(".");
  if(packet.data_id!=0)
  {
   
    for(int i=0; i<packet.data_count; i++)
    {
      //Serial.print(packet.data[i]);
    }
    switch(packet.data_id)
    {
      case  RC_SRASENSORSBOARD_UVLEDENABLE_DATAID:
      {
        //Serial.println("UV Toggle");
        toggleUvLed();
        break;
      }
      case RC_SRASENSORSBOARD_SPECTROMETERRUN_DATAID:
      {
        //Serial.println("Spectrometer Running");
        digitalWrite(UV_TOGGLE_PIN, HIGH);
        digitalWrite(SW_FLAG1_PIN, HIGH);
        if(!spectrometerRun(A19, packet.data[0], true)) //True prints data to serial
        {
          digitalWrite(SW_ERROR_PIN, HIGH);
          delay (1000);
          digitalWrite(SW_ERROR_PIN, LOW);
        }
        digitalWrite(SW_FLAG1_PIN, LOW);
        digitalWrite(UV_TOGGLE_PIN, LOW);
      }
    }
  }

  static int timer = 0;

  if(timer > millis()) timer = millis();
  
  if(millis()-timer>=1000)
  {
    bool do_break = false;
    for(int i = 0; i<5; i++)
    {
      Serial.println(SRADATA[i]);
      if(SRADATA[i] == 0) do_break = true;
    }
    if(1)//!do_break)
    {
      Serial.println("Sending//////////////////////////////////////");
      timer = millis();
      Rovecomm.write(RC_SRASENSORSBOARD_SENSORDATA_HEADER, SRADATA);
    }
  }
  
  
  delay(ROVECOMM_DELAY);
}



//SHT-10 Sensor code for soil Temp and Moisture levels 
void readSHT10()
{
  moisture = th_sensor.readHumidity();
  temperature_soil = th_sensor.readTemperatureC();
  Serial.print("Temperature: ");Serial.print(temperature_soil);Serial.print(" C, Humidity: ");Serial.print(moisture);Serial.println(" ");
}



//AM2302 Code for Temp and Humidity.
void readAM2302()
{
  humidity_atm = dht.readHumidity();
  temperature_atm = dht.readTemperature();
  Serial.print(F("Humidity: "));Serial.print(humidity_atm);Serial.print(F("% Temperature: "));Serial.print(temperature_atm);Serial.print(F(" C "));Serial.println((""));
}



//MQ-4 Code for reading Methane Values
void mthnSensorMQ4()
{
  delay(100); //Long delay will slow down code immensly
  uint16_t adc_reading = analogRead(METHANE_VOUT_PIN);
  Serial.print("Methane ADC:");  
  Serial.println(adc_reading);
  methanePpm = adc_reading;//map(adc_reading, METHANE_ADC_LOW, METHANE_ADC_HIGH, METHANE_ACTUAL_LOW, METHANE_ACTUAL_HIGH);//300 - 10,000 are in parts per million.(units)
  constrain(methanePpm, 0, 65535); //to cast to lower unit
  Serial.println("Methane Actual:");
  Serial.println(methanePpm, DEC);
  
}

//Indicates an Error with the SHT-10:
//If flashing most likely cause is connection issues
void indicateSensorErrorSHT10(float moisture, float temperature_soil)
{
  if((isnan(temperature_soil) && isnan(moisture)))
  {
    Serial.println(("Failed to read from the SHT10 sensor!"));
    digitalWrite(SW_ERROR_PIN, HIGH);
    delay (600);
    digitalWrite(SW_ERROR_PIN,LOW);
    delay (300);
    return;
  }
}



//Indicates an error with the AM2302 Sensor.
void indicateSensorErrorAM2302(float humidity_atm, float temperature_atm)
{
  if((isnan(temperature_atm) && isnan(humidity_atm)))
  {
    Serial.println(("Failed to read from the AM2302 sensor!"));
    digitalWrite(SW_ERROR_PIN, HIGH);
    delay (600);
    digitalWrite(SW_ERROR_PIN,LOW);
    delay (300);
    return;
  }
}



//Toggles our UV Led on and off through rovecomm.
void toggleUvLed()
{
  if(packet.data[0] == 1) //RC_SRASENSORSBOARD_UVLEDENABLE_ENABLED)
  {
    digitalWrite(UV_TOGGLE_PIN, HIGH);
  }
  else
  {
    digitalWrite(UV_TOGGLE_PIN, LOW);
  }
}

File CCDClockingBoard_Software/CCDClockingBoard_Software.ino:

#include "inc/tm4c1294ncpdt.h"
#include "inc/hw_gpio.h"
//#include "roveAttachTimerInterrupt.h"

#define NUM_PIXELS 3694
#define COUNTS_PER_PIXEL 8
#define NUM_COUNTS (NUM_PIXELS+4)*COUNTS_PER_PIXEL-1
#define COUNTS_TO_DUMMY 256+3648*8
//Master clock=callfreq/2
//SH = Master clock freq/8 = callfreq/16
//ICG low for first 16 calls (first SH), high the rest

///////////////////
//Pin Map
//PE0-Master Clock
//PE1-ICG
//PE2-CCD_INT_1
//PE3-SH
//PE4-CCD_INT_2

uint16_t count = 0;

void writeClock();

void setup() {
  Serial.begin(9600);
  delay(10);
  Serial.println("init");

  // start the SPI library:
  pinMode(PE_0, OUTPUT);
  pinMode(PE_1, OUTPUT);
  pinMode(PE_2, OUTPUT);
  pinMode(PE_3, OUTPUT);
  pinMode(PE_4, OUTPUT);
  pinMode(PE_5, OUTPUT);

  digitalWrite(PE_0, HIGH);
  digitalWrite(PE_1, HIGH);
  digitalWrite(PE_2, HIGH);
  digitalWrite(PE_3, HIGH);
  digitalWrite(PE_4, HIGH);
  digitalWrite(PE_5, HIGH);

  //roveAttachTimerInterruptTicks24( writeClock,  T0_A, TIMER_INTERRUPT_USE_PISOC,    30, 7 );
  //roveAttachTimerInterruptTicks24( writeClock,  T0_A, TIMER_INTERRUPT_USE_SYSCLOCK, 1, 0 );

  delay(100);
}
void loop() {
  int count1 = 0;
  int start_micros = micros();
  while (1)
  {
    writeClock();
    //count1++;
  }
  Serial.println(count1);

}

void writeClock()
{
  if (count == 7)                    HWREG(GPIO_PORTE_BASE + (B00001011 << 2)) = (B00000001);
  else if (count == 24)              HWREG(GPIO_PORTE_BASE + (B00001011 << 2)) = (B00001010);
  else if (count == 255)             HWREG(GPIO_PORTE_BASE + (B00001101 << 2)) = (B00000101);
  else if (count == COUNTS_TO_DUMMY) HWREG(GPIO_PORTE_BASE + (B00001101 << 2)) = (B00001000);
  else                               HWREG(GPIO_PORTE_BASE + (B00011001 << 2)) = (count & B00011001);
  count < NUM_COUNTS ? count++ : count = 0;
}
